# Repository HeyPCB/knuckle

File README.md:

# Knuckle

A 35 mm round FOC driver that bolts to a GBM2804 gimbal motor and answers on the Open Duck Mini's servo bus as an STS3215.

Part of [HeyPCB's open robot boards](https://github.com/HeyPCB). Designed end to end with the HeyPCB method on
KiCad 10 (headless pipeline, Freerouting 2.4.1); every number below is measured on the files in this repository.
Mentions of `./run.sh`, `docs/rules/`, `blocks/` or `parts/` refer to the heypcb-kicad SDK that produced them.

| Layers | Outline | Parts | Nets | Connections routed | Vias | ERC errors | DRC errors / unconnected / parity |
|---|---|---|---|---|---|---|---|
| 6 | 35 mm round | 45 | 34 | 121 -> 0 open | 67 | 0 | 0 / 0 / 0 |

**Not fabricated, assembled or powered.**

| | |
|---|---|
| KiCad project | [`kicad/`](kicad/) |
| Gerbers (unzipped and zipped), BOM, CPL, STEP, schematic PDF | [`fab/`](fab/) |
| Printed parts (STEP/STL), CadQuery source, fit report | [`cad/`](cad/) |
| Renders | [top](media/top.png), [bottom](media/bottom.png) |
| Design process, every step as KiCad rendered it | [`media/design-process.mp4`](media/design-process.mp4) |

Knuckle is a 35 mm round field-oriented-control (FOC) driver that mounts on the back of an iPower
GBM2804H-100T gimbal motor and answers on the Open Duck Mini's Feetech STS servo bus as an STS3215
(model 777). It is meant as a drop-in for the duck's `head_yaw` (ID 32) and `head_roll` (ID 33)
joints. It was designed with the HeyPCB method on KiCad 10 (the headless heypcb-kicad pipeline,
KiCad 10.0.6, routed by Freerouting 2.4.1) from the brief in `board.json`, following the research
spec in `robots/research/actuator/spec.md`.

**It has not been fabricated, assembled or powered, and its firmware is not written.** The STS3215
emulation below is what that firmware must do; none of it exists yet. Every gate number below is
read from the final run's `report.json`. What this README says about copper, pours, pads and
silkscreen was read from `kicad/knuckle.kicad_pcb` with KiCad 10.0.6's pcbnew, and every
mechanical number was measured on the solids by `cad/parts.py` (`cad/fit.json`).
Numbers marked (est.) are estimates or come from the spec; they are not measurements.

- **MCU:** STM32G431KBU6 (UFQFPN-32, 5 x 5 mm, Cortex-M4F at 170 MHz) on its internal HSI16 clock, at the centre of the top face. SWD on a Tag-Connect TC2030-NL footprint on the bottom (nothing to fit).
- **Driver:** TI DRV8311H, a 3-20 V three-phase bridge (5 A peak, 210 mOhm high + low side) with three integrated low-side current-sense amplifiers. 3x PWM mode: TIM1 drives INHA/B/C, and one enable line drives all three INLx.
- **3.3 V rail:** the DRV8311's own AVDD regulator. There is no buck (see *Decisions*).
- **Encoder:** MagnTek MT6701QT (QFN-16, 14-bit, SSI) exactly on the motor axis on the motor-facing (bottom) face, under the shaft magnet, with its 100 nF. Nothing else is on the bottom face inside an 11 x 11 mm square around the axis.
- **Bus:** two Molex Mini-SPOX 5267-03A vertical sockets (pin 1 DATA, 2 battery, 3 GND) wired in parallel for daisy-chaining, opposite each other on the vertical axis. An SN74LVC1G126 drives DATA from USART2 TX while the USART's hardware DE is high; an SN74LVC1G125 passes DATA to RX while DE is low. DATA has 100 R in series, a 10k pull-up and a 5 V ESD diode.
- **Power in:** the 2S battery from the bus (6.0-8.4 V) through an AO3401A reverse-polarity P-FET, an SMAJ12A TVS and a 22 uF / 25 V polymer tantalum bulk capacitor.
- **Sensing:** motor-rail voltage (100k / 22k) and a 10k NTC beside the driver.
- **Other:** a red status LED; the motor's three phase leads solder into plated holes at the right rim; four radial screw slots for the motor's base pattern.
- **Board:** a 35.0 mm circle (the motor's own diameter), 6 layers, 1.6 mm. F.Cu, In1 a GND plane, In2-In4 and B.Cu routed; after routing F.Cu and B.Cu are poured GND, In2 and In4 VBAT, In3 VM.

## Scope: head joints only

The spec's answer, which this board follows: a 2804-class gimbal motor on a 2S pack cannot replace an
STS3215 in a duck leg, direct or geared. The numbers are the spec's (sections 0 and 2; model outputs
and MuJoCo static torques, not bench measurements):

| | Stall torque | Speed | Note |
|---|---|---|---|
| STS3215, 7.4 V (datasheet) | 1.91 N·m | 5.45 rad/s | what the duck's legs use |
| GBM2804H-100T, direct drive, 7.4 V | 0.047 N·m (est.) | 110 rad/s (est.) | 2.5 % of the STS3215; continuous rating 0.025-0.034 N·m (vendor's load torque) |
| GBM2804H-100T + 36:1 planetary | 1.26 N·m (est.) | 3.1 rad/s (est.) | still short of the STS3215 on both |
| Static load, `knee` (single support) | 1.02-1.08 N·m | | |
| Static load, `hip_roll` (single support) | 0.89-0.92 N·m | | |
| Static load, `neck_pitch` / `head_pitch` | 0.053-0.075 N·m | | needs at least 1:5 gearing (est.) |
| Static load, `head_yaw` / `head_roll` | 0.000 / 0.001-0.016 N·m | | **within the direct-drive motor's continuous rating** |

At 7.4 V every gimbal winding the spec checked (5-11 Ohm) is voltage-limited to about 1.2-2.7 W of
mechanical power (est.), against the STS3215's 2.6 W (datasheet) to 4.5 W (identified model). So
v1 is a direct-drive head actuator: the MT6701 under the shaft magnet is the absolute joint
encoder, with no gearbox, no backlash and no second encoder, and the duck's runtime keeps working
unchanged because the board answers as model 777 at the same IDs and registers. **The ten leg
joints, `neck_pitch` and `head_pitch` stay on STS3215.**

## Decisions and substitutions

| The spec says | On the board | Why |
|---|---|---|
| 3V3 from the DRV8311's AVDD (TTL variant) or an AP63203 buck | **AVDD** | The load is the MCU, the MT6701, CSAREF, the bus buffers and the LED: about 54 mA (the spec's 68 mA budget without the external encoder v1 does not have; est.), inside AVDD's 100 mA. AVDD then dissipates (8.4 - 3.3) V x 54 mA = 0.28 W in the driver (est.); the spec puts the driver's total at 0.76 W or less with 68 mA, about 40-45 C above ambient inside a cover (est.). The buck would add a 4 x 4 mm inductor and about 55 mm² of courtyard (spec: 425 vs 370 mm²) to a board that did not route on four layers without it. Neither margin is measured: see *Check these before ordering* |
| nSLEEP "pull it up" | 100k from **VM**, clamped by an MM5Z5V1 5.1 V zener | Sleep turns AVDD off (TI SLVSFN2B 8.4.1.1), and nSLEEP has a 230-300k internal pull-down. Pulled up from AVDD, the part would never wake. 100k from VM gives about 4.2 V at VM 6.0 V (VIH 1.65 V max); the zener keeps the pin under its 5.5 V recommended maximum up to the TVS's 19.9 V clamp |
| SLEW 47k to AGND (75 V/us) | SLEW tied to AGND (**35 V/us**) | One part and one net fewer on the tightest spot of the board, and the slowest, quietest edge. Cost: about 33 mW of switching loss per phase at stall (est.) |
| GAIN with a 47k footprint for a geared v2 | GAIN left open (1 V/A), no footprint | At 1 V/A the CSAs read about ±1.4 A around 1.65 V, against this motor's 0.92 A peak stall current (est.) |
| 47 uF / 16 V polymer, 3528 | **22 uF / 25 V polymer tantalum** T521B226M025ATE100 (C696813, 100 mOhm) | The live catalogue's B-case rows at 16 V and up offered 47 uF only as MnO2 tantalum (CA45), a poor partner for a low-impedance Li-ion pack. Table 8-1 of the datasheet asks for at least 10 uF on VM; the board has 22 uF + 2 x 10 uF |
| 4 layers | **6 layers** | Measured on 2026-10-02: on 4 layers (F / In1 GND / In2 / B) three placements routed 122 -> 8, 122 -> 4 and 121 -> 5 open, every time into the 0.4 mm-pitch driver whose escape lanes the screw slots squeeze. The full sequence is in `docs/rules/pipeline.md` |
| 4 x Ø2.2 mm M2 holes on Ø16 / Ø19, turned 45° | **4 radial slots**, 3.4 mm wide, screw centres from r = 8.0 to 9.5 mm on the diagonals | The base pattern is not confirmed (spec 2.4). The slots take M2 or M3 on the 16 mm pair (r = 8.0), the 19 mm pair (r = 9.5) and a 12 mm square (r = 8.49), turned 45° so no screw lands under a bus socket. A 12 mm *diameter* pattern (r = 6.0) does not fit them. **Measure before ordering** |
| Phase tracks 0.2-0.3 mm (this board's request; spec 4.7 accepts 0.2 mm) | MOTOR class **0.25 mm**, all on F.Cu; one 2.26 mm stretch of PHASE_B at 0.187 mm | 0.25 mm is the widest track that enters the DRV8311's 0.2 mm OUTx pads at 0.4 mm pitch. The 0.187 mm stretch is the router's, beside pin 11 (see *Phase current and copper*): 0.71 A on 1 oz outer, against 0.65 A RMS at an 8.4 V stall |
| Motor phase pads 3 x 1.5 x 2.5 mm (est.) | KiCad's 1 x 3 solder-wire land (`SolderWire-0.15sqmm_1x03_P4mm_D0.5mm_OD1.5mm`) | Three plated holes at 4 mm pitch at the right rim, in the order of the driver's OUTC/B/A pins, so the phases fan out on F.Cu without crossing. Marked do-not-populate (nothing to buy) |
| RS-485 / CAN as stuffing options; a 6-pin port for a second encoder | **Not on v1** | Both are for a geared v2. A transceiver's 50+ mA does not fit AVDD's budget (it needs the buck and, for CAN, a crystal), and the board already needed six layers. PA11 / PA12 (FDCAN1) are left unconnected for a CAN variant |
| Pin plan: enable PB5, sense PA4 / PA6 / PA7, VBUS PB0, nFAULT PB7, LED PF1 | enable **PB0**, sense **PA5 / PA6 / PA7**, VM **PA4**, NTC **PA0**, nFAULT **PF0**, LED **PB6** | The MCU is turned 90° so its ADC and enable pins face the driver; the pins were moved to the ones on that edge. All three phase currents stay on ADC2, as SimpleFOC's low-side sensing on the G4 wants |
| J1 "IN", J2 "OUT" | Front silkscreen **KNUCKLE** at J1 and **STS BUS** at J2 | The sockets are wired in parallel, so neither is an input. The board name had no other free spot on the front |

The MCU pins (read back from the board's U1 pads; functions from the KiCad symbol's own alternates):

| Pin | Net | Function |
|---|---|---|
| PA8 / PA9 / PA10 | PWM_A / PWM_B / PWM_C | TIM1_CH1 / CH2 / CH3 -> DRV8311 INHA / INHB / INHC |
| PB0 | DRV_EN | DRV8311 INLA + INLB + INLC. 100k pull-down: all three half bridges stay Hi-Z while the MCU is in reset |
| PA5 / PA6 / PA7 | ISENSE_A / B / C | ADC2_IN13 / IN3 / IN4 <- SOA / SOB / SOC |
| PA4 | VM_SENSE | ADC2_IN17, VM x 22 / 122 (8.4 V reads 1.51 V) |
| PA0 | TEMP | ADC1_IN1, 10k NTC (B 3380) under a 10k pull-up |
| PF0 | NFAULT | DRV8311 nFAULT, 5.1k to 3V3 |
| PA1 / PA2 / PA3 | BUS_DE / BUS_TX / BUS_RX | USART2_DE / TX / RX. DE has a 100k pull-down, so the board never drives the bus in reset |
| PA15 / PB3 / PB4 | ENC_CS / ENC_CLK / ENC_DO | SPI1_NSS / SCK / MISO -> MT6701 CSN / CLK / DO. PA15 comes out of reset with a pull-up, so CSN idles high |
| PA13 / PA14 / NRST | SWDIO / SWCLK / NRST | Tag-Connect. SWO is left open: PB3 is the encoder clock |
| PB6 | LED_STAT | red LED through 1k |
| PB8 | BOOT0 | 10k pull-down: boots from flash |
| PF1, PA11, PA12, PB5, PB7 | none | not connected |

## Phase current and copper

**Phase current**, from the spec's per-phase resistance (Rs = 5.292 Ohm, ST motor profiler) at the
voltage-limited stall, where SVPWM puts VM / sqrt(3) across each phase (est.):

| Pack | Peak | RMS | DC into the bridge |
|---|---|---|---|
| 7.4 V (nominal 2S) | 0.81 A | 0.57 A | 0.70 A |
| 8.4 V (full 2S) | 0.92 A | 0.65 A | 0.79 A |

The DC column is the winding's VM² / (2 Rs) divided by VM: 5.2 W at 7.4 V and 6.7 W at 8.4 V. A 39 g
motor cannot hold that; the spec asks the firmware for an I²t limit above about 0.3 A.

**Track ratings** by IPC-2221 at a 10 C rise (heypcb-kicad's `route.ipc2221_amps`):

| Width | 1 oz outer | 0.5 oz inner | 1 oz inner |
|---|---|---|---|
| 0.187 mm | 0.71 A | 0.21 A | 0.36 A |
| 0.225 mm | 0.81 A | 0.25 A | 0.41 A |
| 0.25 mm (MOTOR class) | 0.88 A | 0.27 A | 0.44 A |
| 0.3 mm (VM class) | 1.00 A | 0.30 A | 0.50 A |
| 0.6 mm (VBAT class) | 1.65 A | 0.50 A | 0.83 A |

**Where the copper ran:**

- **All three phases are on F.Cu, 1 oz outer copper, with no vias:** PHASE_A 3.3 mm at 0.25 mm; PHASE_B 4.95 mm, of which 2.26 mm at 0.187 mm and 2.69 mm at 0.25 mm; PHASE_C 7.24 mm at 0.25 mm. Freerouting laid PHASE_B's first stretch out of pin 11 at 0.187 mm, between PHASE_A's track and pin 12, and the import's widening step, which checks 0.2 mm to other nets, could not restore 0.25 mm there. **That stretch is below the 0.2-0.3 mm asked for.** The narrowest phase copper, 0.187 mm, carries 0.71 A against 0.65 A RMS at 8.4 V; the 0.25 mm runs carry 0.88 A. The 0.25 mm class is the widest track that enters the DRV8311's single 0.2 mm OUTx pads at 0.4 mm pitch with 0.15 mm to the next pin, because Freerouting runs without neck-down.
- A tracks-only keepout on In2-In4 between the driver's outputs and the motor holes (`phase_lane_outer_only`) keeps the phases on outer copper. On the route before it, PHASE_C took 6.8 mm of In2, where 0.25 mm carries 0.27 A at 0.5 oz.
- **VM** is 72.25 mm of track. The bridge current leaves Q1 on 0.3 mm of F.Cu, drops through one 0.6 / 0.3 mm via into the In3 VM pour, and comes up through another next to C9, at the driver. The In3 VM pour is one island of 609.8 mm² that joins all five VM vias. Its narrowest cut between those two vias is 2.8 mm (a vertex max-flow on a 0.1 mm raster, more than 1 mm from either via, which can only undercount): about 1.5 A at 0.5 oz inner. 7.35 mm of VM's F.Cu is 0.225 mm: 4.1 mm among the driver's VM pins and capacitors, which the bridge current crosses (0.81 A on 1 oz outer, against 0.79 A DC at an 8.4 V stall), and 3.2 mm on the TVS's branch. A via's 25 um barrel around a 0.3 mm drill is about 1.8 A by the same formula with the outer constant.
- **VBAT** (the bus pass-through) is a 0.6 mm track on In4 from J1 pin 2 to J2 pin 2 along the left rim, inside the In4 VBAT pour; In2 is poured VBAT as well, as the spec asks. Each pour is one island (In2 659.6 mm², In4 679.6 mm²). Between the two sockets, more than 1.5 mm from either pad centre, the narrowest cut is 2.8 mm on In2 and 4.1 mm on In4: together about 3.5 A at 0.5 oz inner. At each socket the pours join pin 2 through 0.4 mm thermal spokes: 1.6 mm of copper per layer within 1 mm of the pad centre, about 2.0 A for both layers at 0.5 oz. The Mini-SPOX contact is rated 3 A (catalogue row).

## STS3215 emulation the firmware must implement

Not written. From spec section 5; register facts are cited there by file and line.

- **Bus:** 1 Mbps 8N1 half duplex on USART2 with hardware DE (DEM mode). Parse `FF FF ID LEN INSTR P... CHK` with `CHK = ~(ID + LEN + INSTR + sum P) & 0xFF`; drop bad checksums. Answer only its own ID, and broadcast (254) only in SYNC_READ slots. Honour Return Delay Time (reg 7) and Response Status Level (reg 8).
- **Instructions:** PING, READ, WRITE, SYNC_WRITE (0x83) and SYNC_READ (0x82) are required; REG_WRITE and ACTION are used by the official SDK; RESET is optional.
- **SYNC_READ slotting:** reply after the status packets of every ID listed before its own have passed on the bus, counting them by parsing, with a timeout per missing slot (about 100 us, est.). This is critical: rustypot's `set_kps` SYNC_READs register 22 from all 14 IDs and fails if any one is silent.
- **Registers:** model 777 at 3-4; ID at 5 (flash-backed; `configure_motor.py` sets it); baud at 6 (at least 0 = 1 M); P / D / I at 21 / 22 / 23; mode 33 (0 = position); torque enable 40 (0 = INLx low, bridge Hi-Z); goal position 42 and present position 56 (0-4095 from the MT6701's 14 bits >> 2 plus the homing offset at 31; 2048 = 0 rad; sign-magnitude in bit 15); present speed 58 (steps/s, bit 15 sign); load 60 (bit 10 sign); voltage 62 (0.1 V, from VM_SENSE); temperature 63 (from the NTC); current 69; limits 9 / 11 / 13-15 / 16 / 48; lock 55; acceleration and max velocity 41 / 84 / 85 accepted.
- **Control law:** the identified STS3215 model, `tau = clamp(P x 0.166 x (7.4 x 1.178 / 2.479) x (q_ref - q) - 0.56 x omega - D-term, ±tau_max)`, with `q_ref` slew-limited to 5.29 rad/s, then `Iq = tau / Kt`. The motor's 0.03-0.047 N·m saturates it: at P = 8 the head is stiff only within about ±0.4° (est.).
- **FOC core (SimpleFOC):** `BLDCDriver3PWM(PA8, PA9, PA10, PB0)`, `LowsideCurrentSense(1 V/A, PA5, PA6, PA7)`, `MagneticSensorMT6701SSI(PA15)`, 7 pole pairs, 25 kHz centre-aligned PWM, sensor alignment stored in flash.
- **Protection:** act on nFAULT (the hardware variant retries OCP itself after 5 ms); NTC derating and a motor I²t limit; under-voltage below 6.0 V and over-voltage above 9 V; torque off on a fault with STS error bits 0 (voltage), 2 (overheat) and 5 (overload).
- **What it cannot reproduce:** the STS3215's 0.026 kg·m² reflected armature. A direct-drive head is far more responsive; test that in simulation first (below).

## Measured gates

Final run of 2026-10-02, `./run.sh --board boards/knuckle` with media, from `report.json`:

| Gate | Result |
|---|---|
| Composition | 9 block instances -> 45 parts, 34 nets, 17 no-connects |
| Part binding (`lcsc_pinned.json`) | 43 of 45 parts bound to an LCSC number, 0 unsourced, 0 identity conflicts. J3 (the Tag-Connect footprint) is not in the BOM, and J4 (the motor solder holes) is do-not-populate: there is nothing to buy for either. 11 distinct Extended parts, about $33 in JLC loading fees |
| ERC (`kicad-cli sch erc --severity-all`) | 0 errors, 0 warnings |
| Netlist round trip | identical, 34 nets |
| Freerouting, rung 1, fanout on (kept) | 121 -> **0 open** in 20.7 s, DRC score 0, 55 vias |
| Freerouting, rung 1, fanout off (measured for comparison) | 121 -> 1 open in 41.5 s, DRC score 1, 49 vias |
| Copper | 589 tracks, 55 routing vias, 729.7 mm of track (F.Cu 232.3, In2 107.7, In3 118.7, In4 113.4, B.Cu 157.7). No class was narrowed. After the import 14 segments were widened to their class width and 39 kept narrower where the class width would not clear another net (PHASE_B's 0.187 mm and VM's 0.225 mm among them) |
| Pours (only after a measured 0 open) | GND on F.Cu, In1 and B.Cu; **VBAT on In2 and In4; VM on In3** (`board.pours`); 15 stitching vias (70 vias in all); 0 open after the pour, after stitching and at the end; no island-repair vias |
| Silkscreen | 3 words and the 6 back title lines placed; 11 designators re-seated and 31 hidden where nothing fit; 3 stitching vias displaced; nothing clipped. The STAT and MOTOR words did not land |
| DRC (`--severity-all --schematic-parity`, KiCad 10.0.6) | fresh, **0 errors, 0 unconnected, 0 parity**, 1 warning |
| DFM (`jlcpcb_6layer`) | 0 errors, 1 warning (142 stock-footprint silk strokes at 0.12 mm; the fab prints them at its 0.15 mm minimum) |
| Fab gate | **ready**, no blockers; the JLC CPL corrected 19 rotations |

- **The DRC warning** is `silk_over_copper`: one stroke of D3's (the TVS's) front footprint silk crosses J3's NPTH alignment hole at (4.72, 14.96). The fab clips it.
- **The bus sockets have no 3D body.** KiCad 10.0.6 ships no model for the Molex 5267 series, so the renders show bare pads and `fab/knuckle.step` has no body for J1 and J2. `cad/parts.py` stands in their F.Fab outline (9.9 x 4.9 mm) at the catalogue row's 5.9 mm height.

## Silkscreen

Positions are in mm from the top-left corner of the board's 35 x 35 mm square, +y down; the motor axis is at (17.5, 17.5).

- **Front:** KNUCKLE below J1 at (17.5, 8.4) and STS BUS above J2 at (17.5, 26.6), plus the designators that fit.
- **Back** (the motor-facing side, so readable only before assembly): the title KNUCKLE (1.2 mm, bold) and the lines "STS3215 drop-in", "head_yaw  ID 32", "head_roll ID 33", "rev A" and "unfabricated", each placed where the silk stage found room among the parts; SWD at the Tag-Connect footprint.
- **Not placed:** the brief's STAT word at the LED (D4) and MOTOR word at the phase holes (J4) found no free spot. The phase holes run A, B, C from the bottom: PHASE_A at (31.3, 19.0) on the square pad, PHASE_B at (31.3, 15.0), PHASE_C at (31.3, 11.0). Which motor lead is A does not matter to FOC: the firmware's alignment finds the order.

## Printed parts and fit

`cad/parts.py` (CadQuery 2.8, OCP, trimesh) builds four printed parts around the board's real STEP (`fab/knuckle.step`, solids named by reference) and the real STS3215 horn (`STS3215_03a.step` from SO-ARM100), and measures the fit on the solids. Frame: z = 0 is the motor's base (stator) face, +z toward the board. The motor itself (15 mm tall, Ø35, a Ø7 shaft stub protruding 1.2 mm) is the spec's (est.); see *Check these before ordering*.

| Part | What it is | Measured fit (`fit.json`) |
|---|---|---|
| Magnet holder | Cup pressed on the shaft stub: OD 9.0, bore 6.98 x 1.0 deep, floor 0.6, pocket Ø6.05 x 2.5 for the 6 x 2.5 mm diametric magnet. Print in PETG, or turn in brass or aluminium; never steel | Rides from z 0.2 to 4.3 (0.2 mm above the base face). Closest bottom part: C13 at 1.285 mm |
| Air gap | | **1.000 mm** magnet face to MT6701 face (target 1.0, window 0.5-2.0). The MT6701 stands 0.785 mm below the board's bottom face in the STEP and sits **0.0 mm** off the axis (limit 0.3) |
| Standoff | A ring (ID 11, OD 25, 1.5 thick) with four Ø5.6 bosses at the screw points: the 16 mm pair on the 45° diagonal and the 19 mm pair on the 135° one | Height **6.085 mm** = 4.3 (magnet face) + 1.0 (gap) + 0.785 (encoder body). Ring to holder 1.0 mm radially. Closest bottom part: R4 at 0.611 mm |
| Cover | Ø38.0 (wall 1.2, 0.3 mm radial clearance to the board), roof 2.0 mm; the skirt stops at the motor's base plane, clear of the spinning rotor. Posts with M2 counterbores at the screw points; four M3 heat-set insert bosses (Ø4.0 x 4.5) on a Ø28 circle at 20°, 160°, 200° and 340° for the robot-side mount; a 6 x 2 mm lead notch at +X, where the phase holes are | Roof underside z 14.165, top z 16.165. Socket openings **10.7 x 5.7 mm** against the 9.9 x 4.9 mm header envelope: 0.4 mm margin each side; header top 0.5 mm below the roof; 0.64 mm from each header to the cover. Closest top part: C4 at 0.527 mm. The tallest top part is D3, the SMA TVS, 2.22 mm above the board (the spec's guideline was 2.0 mm; the roof is set by the headers, so it clears) |
| Horn adapter | Ø23 x 4 (wider than the horn's Ø20 so the rotor slots keep a wall). Joint side: four Ø4.0 holes for M3 heat-set inserts. Rotor side: four radial slots 2.4 mm wide with counterbores, covering bolt circles Ø12.0 to Ø16.98 (12 mm apart across, Ø16, or a 12 mm square: spec 2.4's open conflict), and a Ø7.5 relief | STS3215 horn measured from the STEP: Ø20.0 x 2.5, four Ø2.5 holes at (±4.95, ±4.95), a Ø14.0 bolt circle. The adapter's insert holes read back off the solid at the same four points: **0.0 mm** deviation |
| Screws | | M2: grip 14.16 mm (cover top less the head to the base face) + 3 mm into the motor base = 17.16 mm, so **M2 x 18**, A2 stainless or nylon near the magnet |
| Stack | | Horn face z -19.0 to cover top z 16.165: **35.2 mm** overall, on the motor's estimated 15 mm |

All four STLs read back watertight (standoff 931.2 mm³, magnet holder 150.6, cover 4534.8, horn adapter 1030.3).

Previews (SVG drawn by the script's own hidden-line renderer, PNG by `rsvg-convert`):
- `cad/exploded.svg` / `.png`: horn adapter, motor proxy, magnet holder and magnet, standoff, board, cover;
- `cad/section.svg` / `.png`: a section through the axis, with the air gap, the cover top and the horn face marked.

The parts and `assembly.step` (with a motor proxy) are in `cad/`. The duck's head brackets must still be redrawn in the duck's own CAD for a Ø38 x 35 mm cylinder; that is not part of this project.

## Check these before ordering

The board passes ERC, the netlist round trip, routing, DRC (errors, unconnected and parity), DFM and the fab gate in KiCad. It has not been fabricated, assembled or powered, and it has no firmware.

**Mechanics: measure one GBM2804H-100T first**
- **Base hole pattern and thread.** The slots take M2 or M3 screws on the 16 mm and 19 mm pairs (r = 8.0 and 9.5) and on a 12 mm square (r = 8.49). They do **not** take a 12 mm-diameter pattern (r = 6.0). The thread is M2 per iFlight's GM2804 answer; HobbyKing users report tapping M3. `cad/parts.py` takes the pattern from `MOTOR["base_pairs"]`.
- **Shaft stub, base face and diameter.** The magnet holder assumes a Ø7 shaft protruding 1.2 mm (an unlicensed CAD parameter, cross-check only). That number sets the holder, and through it the standoff height and the 1.000 mm air gap; the 0.5-2.0 mm window tolerates about ±0.5 mm of error. Also check that the base face is flat where the standoff bosses sit, and the Ø35 the cover skirt assumes.
- **Rotor-top holes** for the horn adapter: "12 mm" centre to centre in two vendor listings, four holes on Ø16 in another model. The adapter's slots cover Ø12 to Ø16.98.
- **Phase leads.** The solder holes are 0.7 mm drills on 1.7 mm pads at 4 mm pitch at the +X rim, where the cover's lead notch is. Check the leads' size, length and exit angle.
- **Header height.** The cover's openings and roof use 5.9 mm from the catalogue row for C45581067, not from Molex's drawing.

**Bus and firmware**
- **Logic-analyser capture of a real STS3215 chain** before writing the bus layer: SYNC_READ slot timing, the units of Return Delay Time, Torque Enable at power-on, whether a Goal Position write enables torque, status packets at Response Status Level 0 and 1. Dump a real servo's registers 0-86 for the defaults.
- **Test in Open_Duck_Playground first.** Change `head_yaw` and `head_roll` to a direct-drive model (about zero armature, 0.03 N·m saturation) and check that the walking policy still holds before flying the board on the robot.
- **Connector pin order.** 1 DATA, 2 VBAT, 3 GND is the Waveshare adapter's order. Check it against a Feetech cable: a cable wired otherwise puts 8.4 V on DATA, and the 74LVC buffers are 5.5 V tolerant.
- **Chain order.** The VBAT class assumes the Knuckles sit at the far end of the neck/head branch. An STS3215 downstream would pass its 2.5 A stall current through J1 and J2: above the 2.0 A at the sockets' thermal spokes at 0.5 oz, inside the Mini-SPOX's 3 A.
- **SWD only before assembly.** The Tag-Connect footprint is on the motor-facing face at r = 13.8 mm, between the standoff and the cover skirt; once mounted, the motor covers it. Flash before mounting, or plan a bootloader over the STS bus. IDs are set over the bus afterwards with the duck's `configure_motor.py`.

**Fab and assembly**
- **Via in pad.** One 0.5 / 0.25 mm GND via at the board centre lies inside both the MCU's exposed pad (top) and the MT6701's (bottom), and one lies in the DRV8311's. Order them filled and capped, or expect solder to wick.
- **Stackup and inner copper.** The gerber job lists 35 um copper on all six layers and 0.274 mm dielectrics: KiCad's default stackup, not a fab's. The ratings above give 0.5 oz and 1 oz inner copper; choose when ordering.
- **Two-sided assembly.** 20 of the 41 SMD parts in the CPL are on the bottom: the MT6701 and its 100 nF, the NTC, both small diodes, 10 of the 13 resistors and 5 more capacitors. Quote it as double-sided.
- **Stock** (live lookups of 2026-10-02; re-check): T521B226M025ATE100 1799, STM32G431KBU6 2114, MT6701QT-STD 5361, DRV8311HRRWR 6703. Every part number in `fab/knuckle_bom.csv` comes from the pinned table; the Knuckle rows are dated 2026-10-02.

**Thermal and electrical (estimates, not measured)**
- **DRV8311.** The spec estimates at most 0.76 W in the driver at an 8.4 V stall (conduction 0.10-0.19 W, switching 0.02-0.09 W, quiescent 0.13 W, AVDD 0.35 W at 68 mA; this board's AVDD share is about 0.28 W), about 40-45 C above ambient inside a cover. Its exposed pad has one via into the In1 plane. Measure the case at stall. If it runs hot, the AP63203 buck takes the AVDD share off (about 18 C less, spec).
- **The motor is the limit.** 5.2 W at a 7.4 V stall and 6.7 W at 8.4 V in a 39 g motor; the firmware needs an I²t limit, and the VM copper at the driver (0.81 A) has almost no margin over a full 8.4 V stall (0.79 A).
- **AO3401A gate.** VGS is -8.4 V on a full pack, inside the part's common ±12 V rating (not read from its datasheet). A surge the TVS clamps at up to 19.9 V exceeds it; the spec's optional 10 V gate-source zener is not fitted.
- **No fuse.** The pass-through is unfused, like the STS3215 it replaces.

## Licences

- **Open Duck Mini** (apirrone/Open_Duck_Mini, Apache-2.0): its MJCF, BOM, wiring diagram and docs were read for the spec. Nothing from it is in this repository.
- **Open_Duck_Mini_Runtime and Open_Duck_Playground** (apirrone): no licence declared. Read only; this README cites facts from them (IDs, registers, the 50 Hz loop), and no code was copied.
- **STS3215 STEP** (TheRobotStudio SO-ARM100, `STEP/SO100/STS3215_03a.step`, Apache-2.0): `cad/parts.py` reads it from the research folder to measure the horn. It is not copied here.
- **rustypot** (Apache-2.0), **lerobot** (Apache-2.0), **FTServo_Python** (MIT), **Rhoban/bam** (Apache-2.0): read; protocol facts and identified parameters cited. **pypot** (GPL-3.0): read only, register addresses cited as facts.
- **Datasheets** (TI SLVSFN2B DRV8311, MagnTek MT6701 Rev 1.8, Waveshare bus-adapter schematics) and the ST motor profile: facts cited, nothing redistributed.
- Knuckle's own brief, blocks, CAD script and this README are the repository's own.

## Files

Committed:
- `board.json`: the brief the pipeline built everything here from.
- `cad/parts.py`: the printed parts and the fit check.
- `README.md`: this file. The blocks are `blocks/knuckle_*.json` (plus the shared `gpio_led`), and the new part numbers are in `parts/lcsc_pinned.json`.

Regenerated by the commands below, under `build/knuckle/` (not committed):
- `report.json`: the run's gate report, the source of every gate number above.
- `knuckle.kicad_pro`, `knuckle.kicad_sch`, `knuckle.kicad_pcb` (routed and poured).
- `fab/knuckle_gerbers.zip` (14 layer and job files, the drill file and the drill map), `fab/knuckle_bom.csv` (24 rows, 43 parts), `fab/knuckle_cpl_jlc.csv` (41 SMD parts, rotations corrected), `fab/knuckle_pos.csv`, `fab/knuckle_schematic.pdf`, `fab/knuckle.step`.
- `render/`: KiCad raytraced frames: `0062_place.png` (placed, in 3D), `0105_3d.png` (top), `0106_3d.png` (bottom) and the turntable `0107_3d.png` to `0167_3d.png`.
- `video/knuckle_design_process.mp4`: the design-process video (113.2 s, 169 frames).
- `cad/`: `standoff`, `magnet_holder`, `cover`, `horn_adapter` (`.step` and `.stl`), `assembly.step`, `fit.json`, `exploded.svg/png`, `section.svg/png`.

## Reproduce

From the heypcb-kicad repository:

```bash
./run.sh --board boards/knuckle              # every stage, with the 3D renders and the video
./run.sh --board boards/knuckle --no-media   # stop before the 3D frames, renders and video
python cad/source/parts.py   # the printed parts and fit.json (a Python with CadQuery and trimesh)
```

`parts.py` needs the fab stage's STEP and refuses to read a board mid-run. It finds the STS3215 STEP in the research folder beside the repository, or takes `--sts-step`.

Placement is fully locked in the brief (45 parts, each with its reason), and Freerouting is given a Specctra file whose order is set by content alone, so the brief routes the same way every time. On 2026-10-02 it was built in full with media twice: once with In2 poured GND and the earlier class notes, and once as committed. Both routed 121 -> 0 open with the same copper (589 tracks, 55 vias, 729.7 mm, the same per-layer lengths); only the solve times differed. The copper, pour and pad figures in this README were measured on the second run's `knuckle.kicad_pcb`.

## License

Hardware: [CERN-OHL-S v2](LICENSE). Files under `cad/` that derive from third-party CAD carry their own notice there.

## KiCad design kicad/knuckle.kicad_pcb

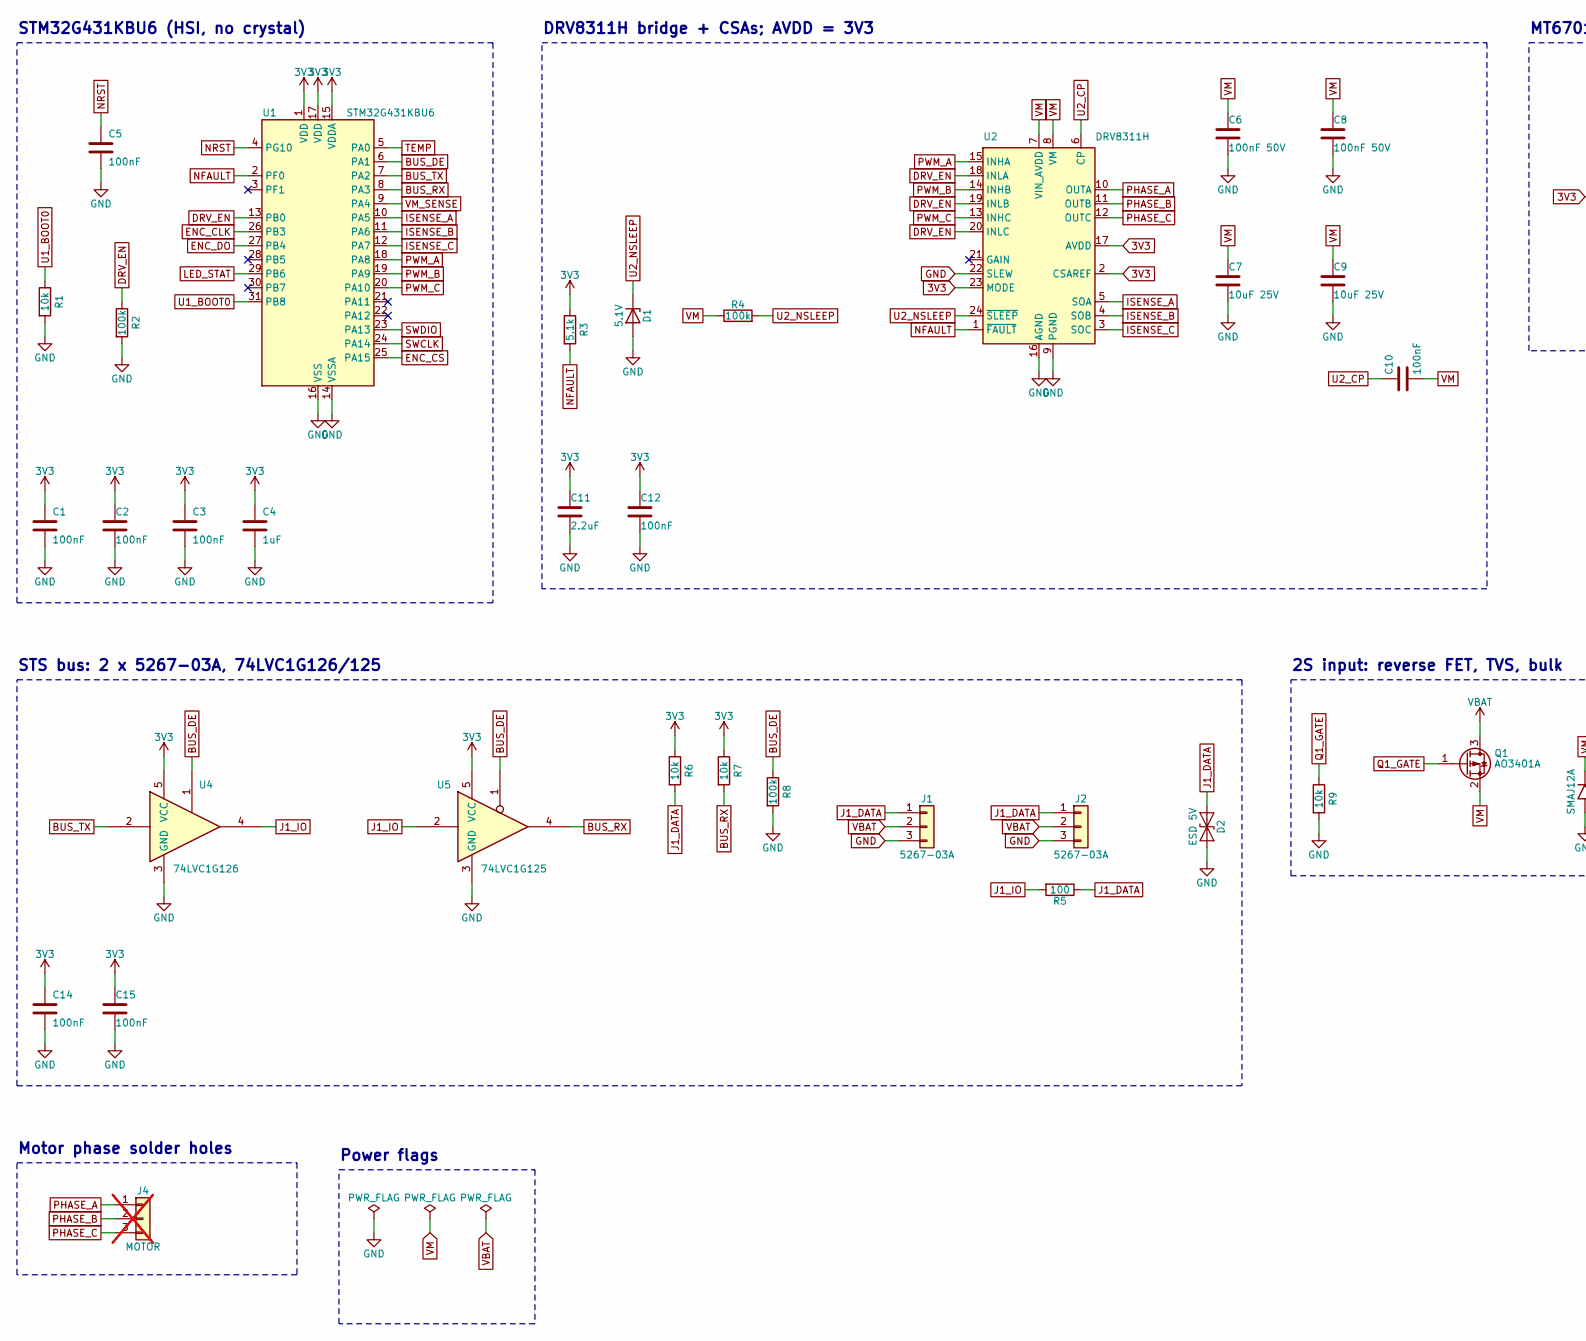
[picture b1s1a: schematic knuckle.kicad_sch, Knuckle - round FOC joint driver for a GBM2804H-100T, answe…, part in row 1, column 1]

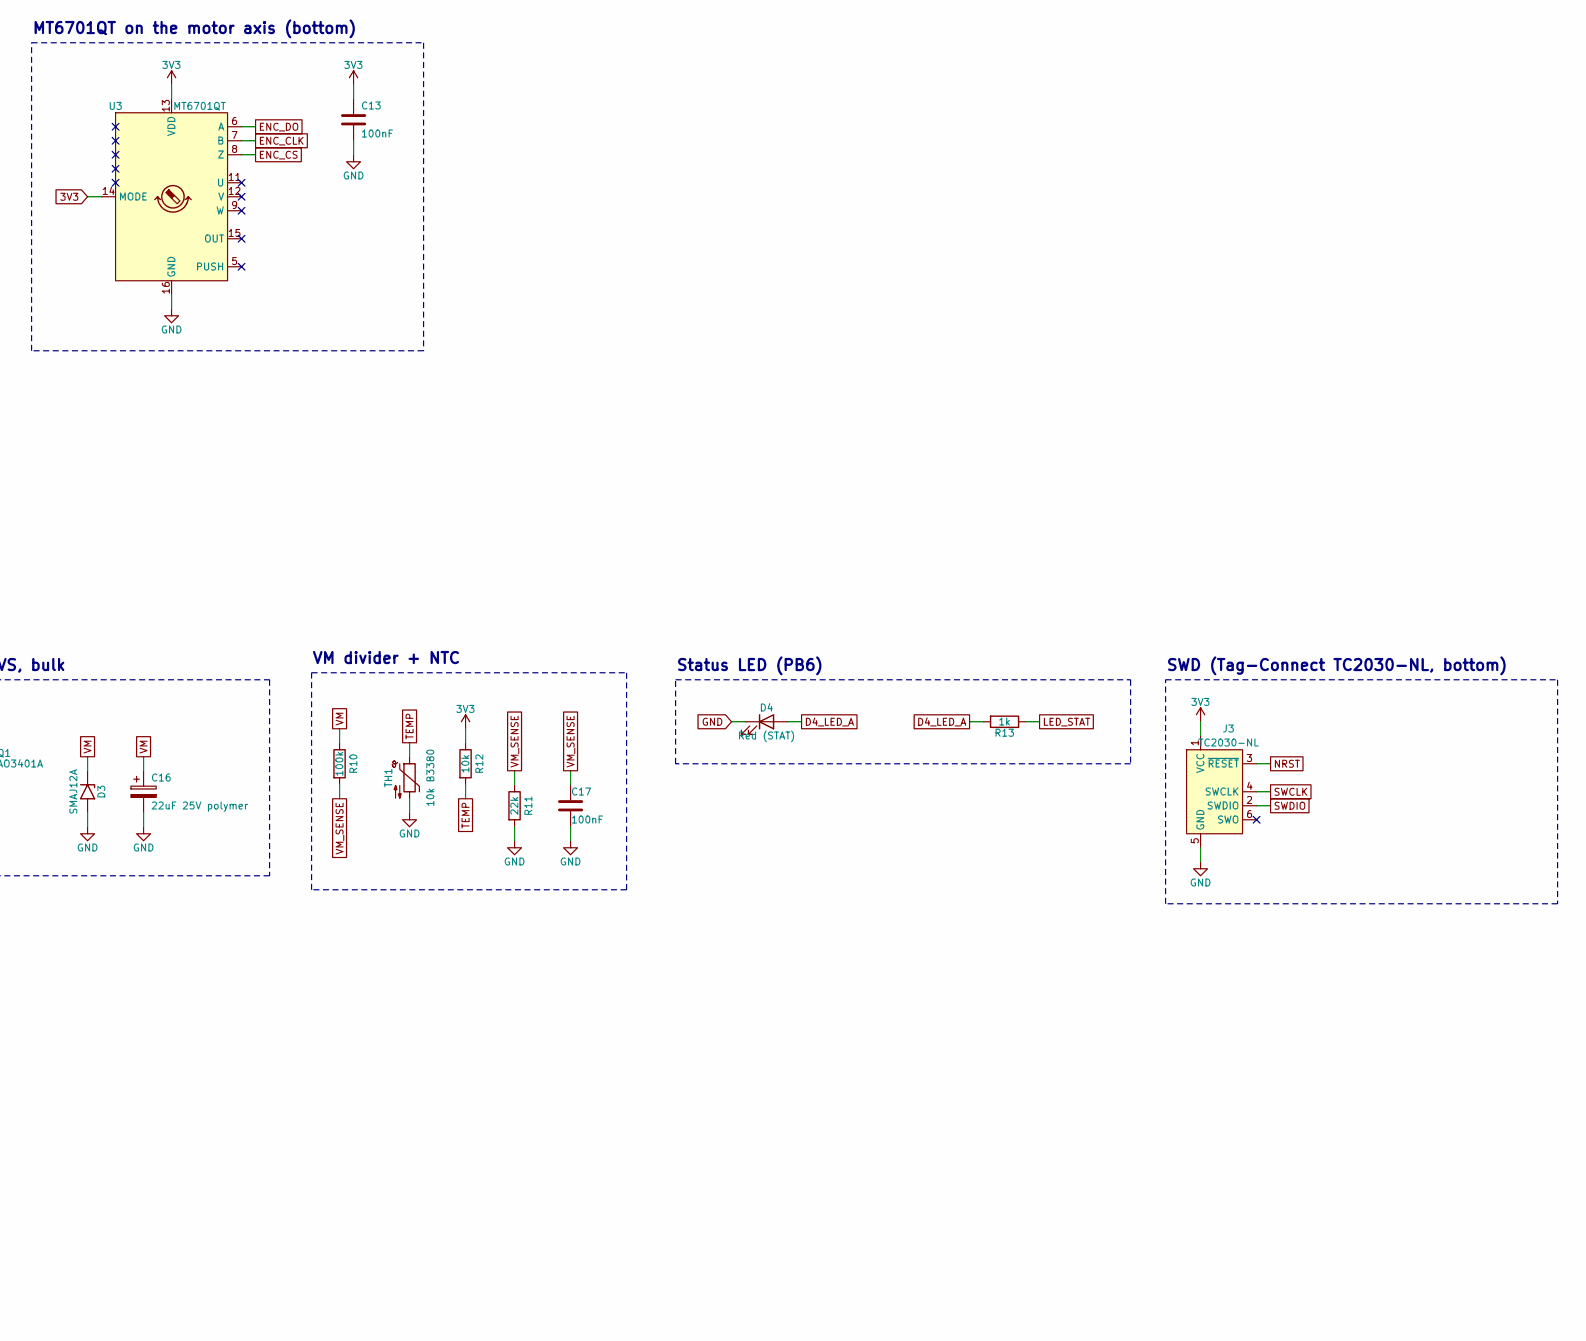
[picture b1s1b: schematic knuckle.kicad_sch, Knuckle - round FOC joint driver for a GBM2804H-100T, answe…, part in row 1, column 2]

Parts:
C1, C2, C3, C5, C10, C12, C13, C14, C15, C17: 100nF; C_0402_1005Metric; MPN CL05B104KO5NNNC; LCSC C1525
C4: 1uF; C_0402_1005Metric; MPN CL05A105KA5NQNC; LCSC C52923
C6, C8: 100nF 50V; C_0402_1005Metric; MPN CL05B104KB54PNC; LCSC C307331
C7, C9: 10uF 25V; C_0603_1608Metric; MPN CL10A106MA8NRNC; LCSC C96446
C11: 2.2uF; C_0402_1005Metric; MPN CL05A225MQ5NSNC; LCSC C12530
C16: 22uF 25V polymer; CP_EIA-3528-21_Kemet-B; MPN T521B226M025ATE100; LCSC C696813
D1: 5.1V; D_SOD-523; MPN MM5Z5V1T1G; LCSC C146754
D2: ESD 5V; D_SOD-923; MPN TPESD9B5.0ST5G; LCSC C2682268
D3: SMAJ12A; D_SMA; MPN SMAJ12A; LCSC C113957
D4: Red (STAT); LED_0603_1608Metric; MPN KT-0603R; LCSC C2286
J1, J2: 5267-03A; Molex_SPOX_5267-03A_1x03_P2.50mm_Vertical; MPN 0022035035; LCSC C45581067
J3: TC2030-NL; Tag-Connect_TC2030-IDC-NL_2x03_P1.27mm_Vertical
J4: MOTOR; SolderWire-0.15sqmm_1x03_P4mm_D0.5mm_OD1.5mm; not fitted
Q1: AO3401A; SOT-23; MPN AO3401A; LCSC C15127
R1, R6, R7, R9, R12: 10k; R_0402_1005Metric; MPN 0402WGF1002TCE; LCSC C25744
R2, R4, R8, R10: 100k; R_0402_1005Metric; MPN 0402WGF1003TCE; LCSC C25741
R3: 5.1k; R_0402_1005Metric; MPN 0402WGF5101TCE; LCSC C25905
R5: 100; R_0402_1005Metric; MPN 0402WGF1000TCE; LCSC C25076
R11: 22k; R_0402_1005Metric; MPN 0402WGF2202TCE; LCSC C25768
R13: 1k; R_0603_1608Metric; MPN 0603WAF1001T5E; LCSC C21190
TH1: 10k B3380; R_0402_1005Metric; MPN NCP15XH103F03RC; LCSC C77131
U1: STM32G431KBU6; QFN-32-1EP_5x5mm_P0.5mm_EP3.45x3.45mm; MPN STM32G431KBU6; LCSC C529358
U2: DRV8311H; Texas_RRW0024A_WQFN-24-1EP_3x3mm_P0.4mm_EP1.9x1.9mm; MPN DRV8311HRRWR; LCSC C5218862
U3: MT6701QT; QFN-16-1EP_3x3mm_P0.5mm_EP1.7x1.7mm; MPN MT6701QT-STD; LCSC C2913974
U4: 74LVC1G126; SOT-23-5; MPN SN74LVC1G126DBVR; LCSC C7834
U5: 74LVC1G125; SOT-23-5; MPN SN74LVC1G125DBVR; LCSC C23654

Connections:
3V3: C1.1, C2.1, C3.1, C4.1, C11.1, C12.1, C13.1, C14.1, C15.1, J3.1 (VCC), R3.1, R6.1, R7.1, R12.1, U1.1 (VDD), U1.15 (VDDA), U1.17 (VDD), U2.2 (CSAREF), U2.17 (AVDD), U2.23 (MODE), U3.13 (VDD), U3.14 (MODE), U4.5 (VCC), U5.5 (VCC)
BUS_DE: R8.1, U1.6 (PA1), U4.1, U5.1
BUS_RX: R7.2, U1.8 (PA3), U5.4
BUS_TX: U1.7 (PA2), U4.2
D4_LED_A: D4.2 (A), R13.2
DRV_EN: R2.1, U1.13 (PB0), U2.18 (INLA), U2.19 (INLB), U2.20 (INLC)
ENC_CLK: U1.26 (PB3), U3.7 (B)
ENC_CS: U1.25 (PA15), U3.8 (Z)
ENC_DO: U1.27 (PB4), U3.6 (A)
GND: C1.2, C2.2, C3.2, C4.2, C5.2, C6.2, C7.2, C8.2, C9.2, C11.2, C12.2, C13.2, C14.2, C15.2, C16.2, C17.2, D1.2 (A), D2.2 (A2), D3.2 (A2), D4.1 (K), J1.3, J2.3, J3.5 (GND), R1.2, R2.2, R8.2, R9.2, R11.2, TH1.2, U1.14 (VSSA), U1.16 (VSS), U1.32 (VSS), U1.33 (VSS), U2.9 (PGND), U2.16 (AGND), U2.22 (SLEW), U2.25 (PGND), U3.16 (GND), U3.17 (GND), U4.3 (GND), U5.3 (GND)
ISENSE_A: U1.10 (PA5), U2.5 (SOA)
ISENSE_B: U1.11 (PA6), U2.4 (SOB)
ISENSE_C: U1.12 (PA7), U2.3 (SOC)
J1_DATA: D2.1 (A1), J1.1, J2.1, R5.1, R6.2
J1_IO: R5.2, U4.4, U5.2
LED_STAT: R13.1, U1.29 (PB6)
NFAULT: R3.2, U1.2 (PF0), U2.1 (~FAULT)
NRST: C5.1, J3.3 (~RESET), U1.4 (PG10)
PHASE_A: J4.1, U2.10 (OUTA)
PHASE_B: J4.2, U2.11 (OUTB)
PHASE_C: J4.3, U2.12 (OUTC)
PWM_A: U1.18 (PA8), U2.15 (INHA)
PWM_B: U1.19 (PA9), U2.14 (INHB)
PWM_C: U1.20 (PA10), U2.13 (INHC)
Q1_GATE: Q1.1 (G), R9.1
SWCLK: J3.4 (SWCLK), U1.24 (PA14)
SWDIO: J3.2 (SWDIO), U1.23 (PA13)
TEMP: R12.2, TH1.1, U1.5 (PA0)
U1_BOOT0: R1.1, U1.31 (PB8)
U2_CP: C10.1, U2.6 (CP)
U2_NSLEEP: D1.1 (K), R4.2, U2.24 (~SLEEP)
VBAT: J1.2, J2.2, Q1.3 (D)
VM: C6.1, C7.1, C8.1, C9.1, C10.2, C16.1, D3.1 (A1), Q1.2 (S), R4.1, R10.1, U2.7 (VIN_AVDD), U2.8 (VM)
VM_SENSE: C17.1, R10.2, R11.1, U1.9 (PA4)

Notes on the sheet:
STM32G431KBU6 (HSI, no crystal)
DRV8311H bridge + CSAs; AVDD = 3V3
MT6701QT on the motor axis (bottom)
STS bus: 2 x 5267-03A, 74LVC1G126/125
2S input: reverse FET, TVS, bulk
VM divider + NTC
Status LED (PB6)
SWD (Tag-Connect TC2030-NL, bottom)
Motor phase solder holes
Power flags

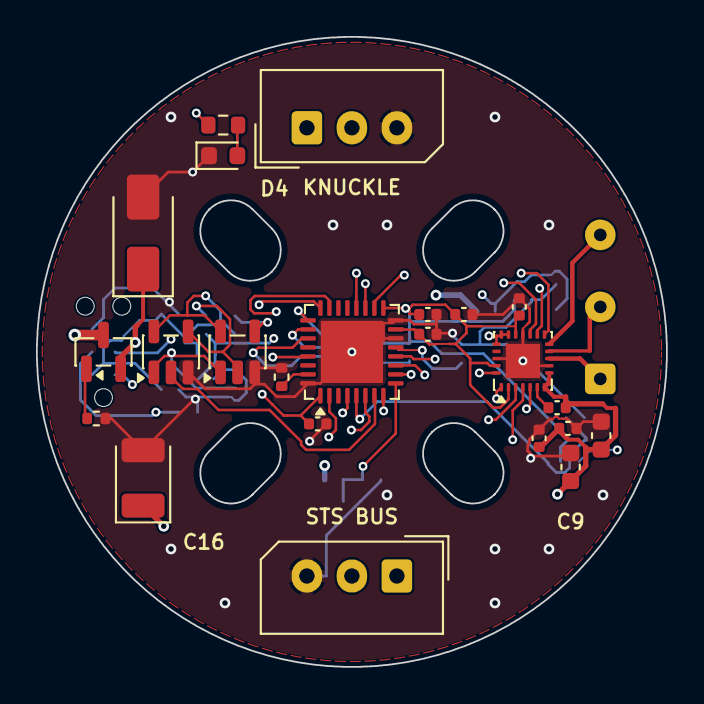
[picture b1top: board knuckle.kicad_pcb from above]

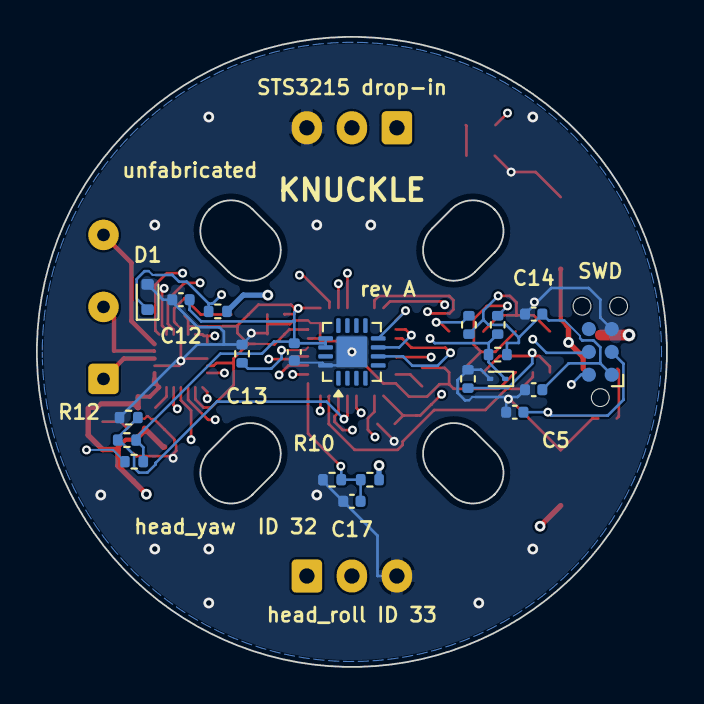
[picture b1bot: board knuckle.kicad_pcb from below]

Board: 6 copper layers, 35.0 x 35.0 mm, 45 parts (21 on the bottom side), 34 nets.

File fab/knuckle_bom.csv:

"Reference","Value","Footprint","MPN","LCSC","Qty"
"C1,C2,C3,C5,C10,C12,C13,C14,C15,C17","100nF","Capacitor_SMD:C_0402_1005Metric","CL05B104KO5NNNC","C1525","10"
"C4","1uF","Capacitor_SMD:C_0402_1005Metric","CL05A105KA5NQNC","C52923","1"
"C6,C8","100nF 50V","Capacitor_SMD:C_0402_1005Metric","CL05B104KB54PNC","C307331","2"
"C7,C9","10uF 25V","Capacitor_SMD:C_0603_1608Metric","CL10A106MA8NRNC","C96446","2"
"C11","2.2uF","Capacitor_SMD:C_0402_1005Metric","CL05A225MQ5NSNC","C12530","1"
"C16","22uF 25V polymer","Capacitor_Tantalum_SMD:CP_EIA-3528-21_Kemet-B","T521B226M025ATE100","C696813","1"
"D1","5.1V","Diode_SMD:D_SOD-523","MM5Z5V1T1G","C146754","1"
"D2","ESD 5V","Diode_SMD:D_SOD-923","TPESD9B5.0ST5G","C2682268","1"
"D3","SMAJ12A","Diode_SMD:D_SMA","SMAJ12A","C113957","1"
"D4","Red (STAT)","LED_SMD:LED_0603_1608Metric","KT-0603R","C2286","1"
"J1,J2","5267-03A","Connector_Molex:Molex_SPOX_5267-03A_1x03_P2.50mm_Vertical","0022035035","C45581067","2"
"Q1","AO3401A","Package_TO_SOT_SMD:SOT-23","AO3401A","C15127","1"
"R1,R6,R7,R9,R12","10k","Resistor_SMD:R_0402_1005Metric","0402WGF1002TCE","C25744","5"
"R2,R4,R8,R10","100k","Resistor_SMD:R_0402_1005Metric","0402WGF1003TCE","C25741","4"
"R3","5.1k","Resistor_SMD:R_0402_1005Metric","0402WGF5101TCE","C25905","1"
"R5","100","Resistor_SMD:R_0402_1005Metric","0402WGF1000TCE","C25076","1"
"R11","22k","Resistor_SMD:R_0402_1005Metric","0402WGF2202TCE","C25768","1"
"R13","1k","Resistor_SMD:R_0603_1608Metric","0603WAF1001T5E","C21190","1"
"TH1","10k B3380","Resistor_SMD:R_0402_1005Metric","NCP15XH103F03RC","C77131","1"
"U1","STM32G431KBU6","Package_DFN_QFN:QFN-32-1EP_5x5mm_P0.5mm_EP3.45x3.45mm","STM32G431KBU6","C529358","1"
"U2","DRV8311H","Package_DFN_QFN:Texas_RRW0024A_WQFN-24-1EP_3x3mm_P0.4mm_EP1.9x1.9mm","DRV8311HRRWR","C5218862","1"
"U3","MT6701QT","Package_DFN_QFN:QFN-16-1EP_3x3mm_P0.5mm_EP1.7x1.7mm","MT6701QT-STD","C2913974","1"
"U4","74LVC1G126","Package_TO_SOT_SMD:SOT-23-5","SN74LVC1G126DBVR","C7834","1"
"U5","74LVC1G125","Package_TO_SOT_SMD:SOT-23-5","SN74LVC1G125DBVR","C23654","1"
